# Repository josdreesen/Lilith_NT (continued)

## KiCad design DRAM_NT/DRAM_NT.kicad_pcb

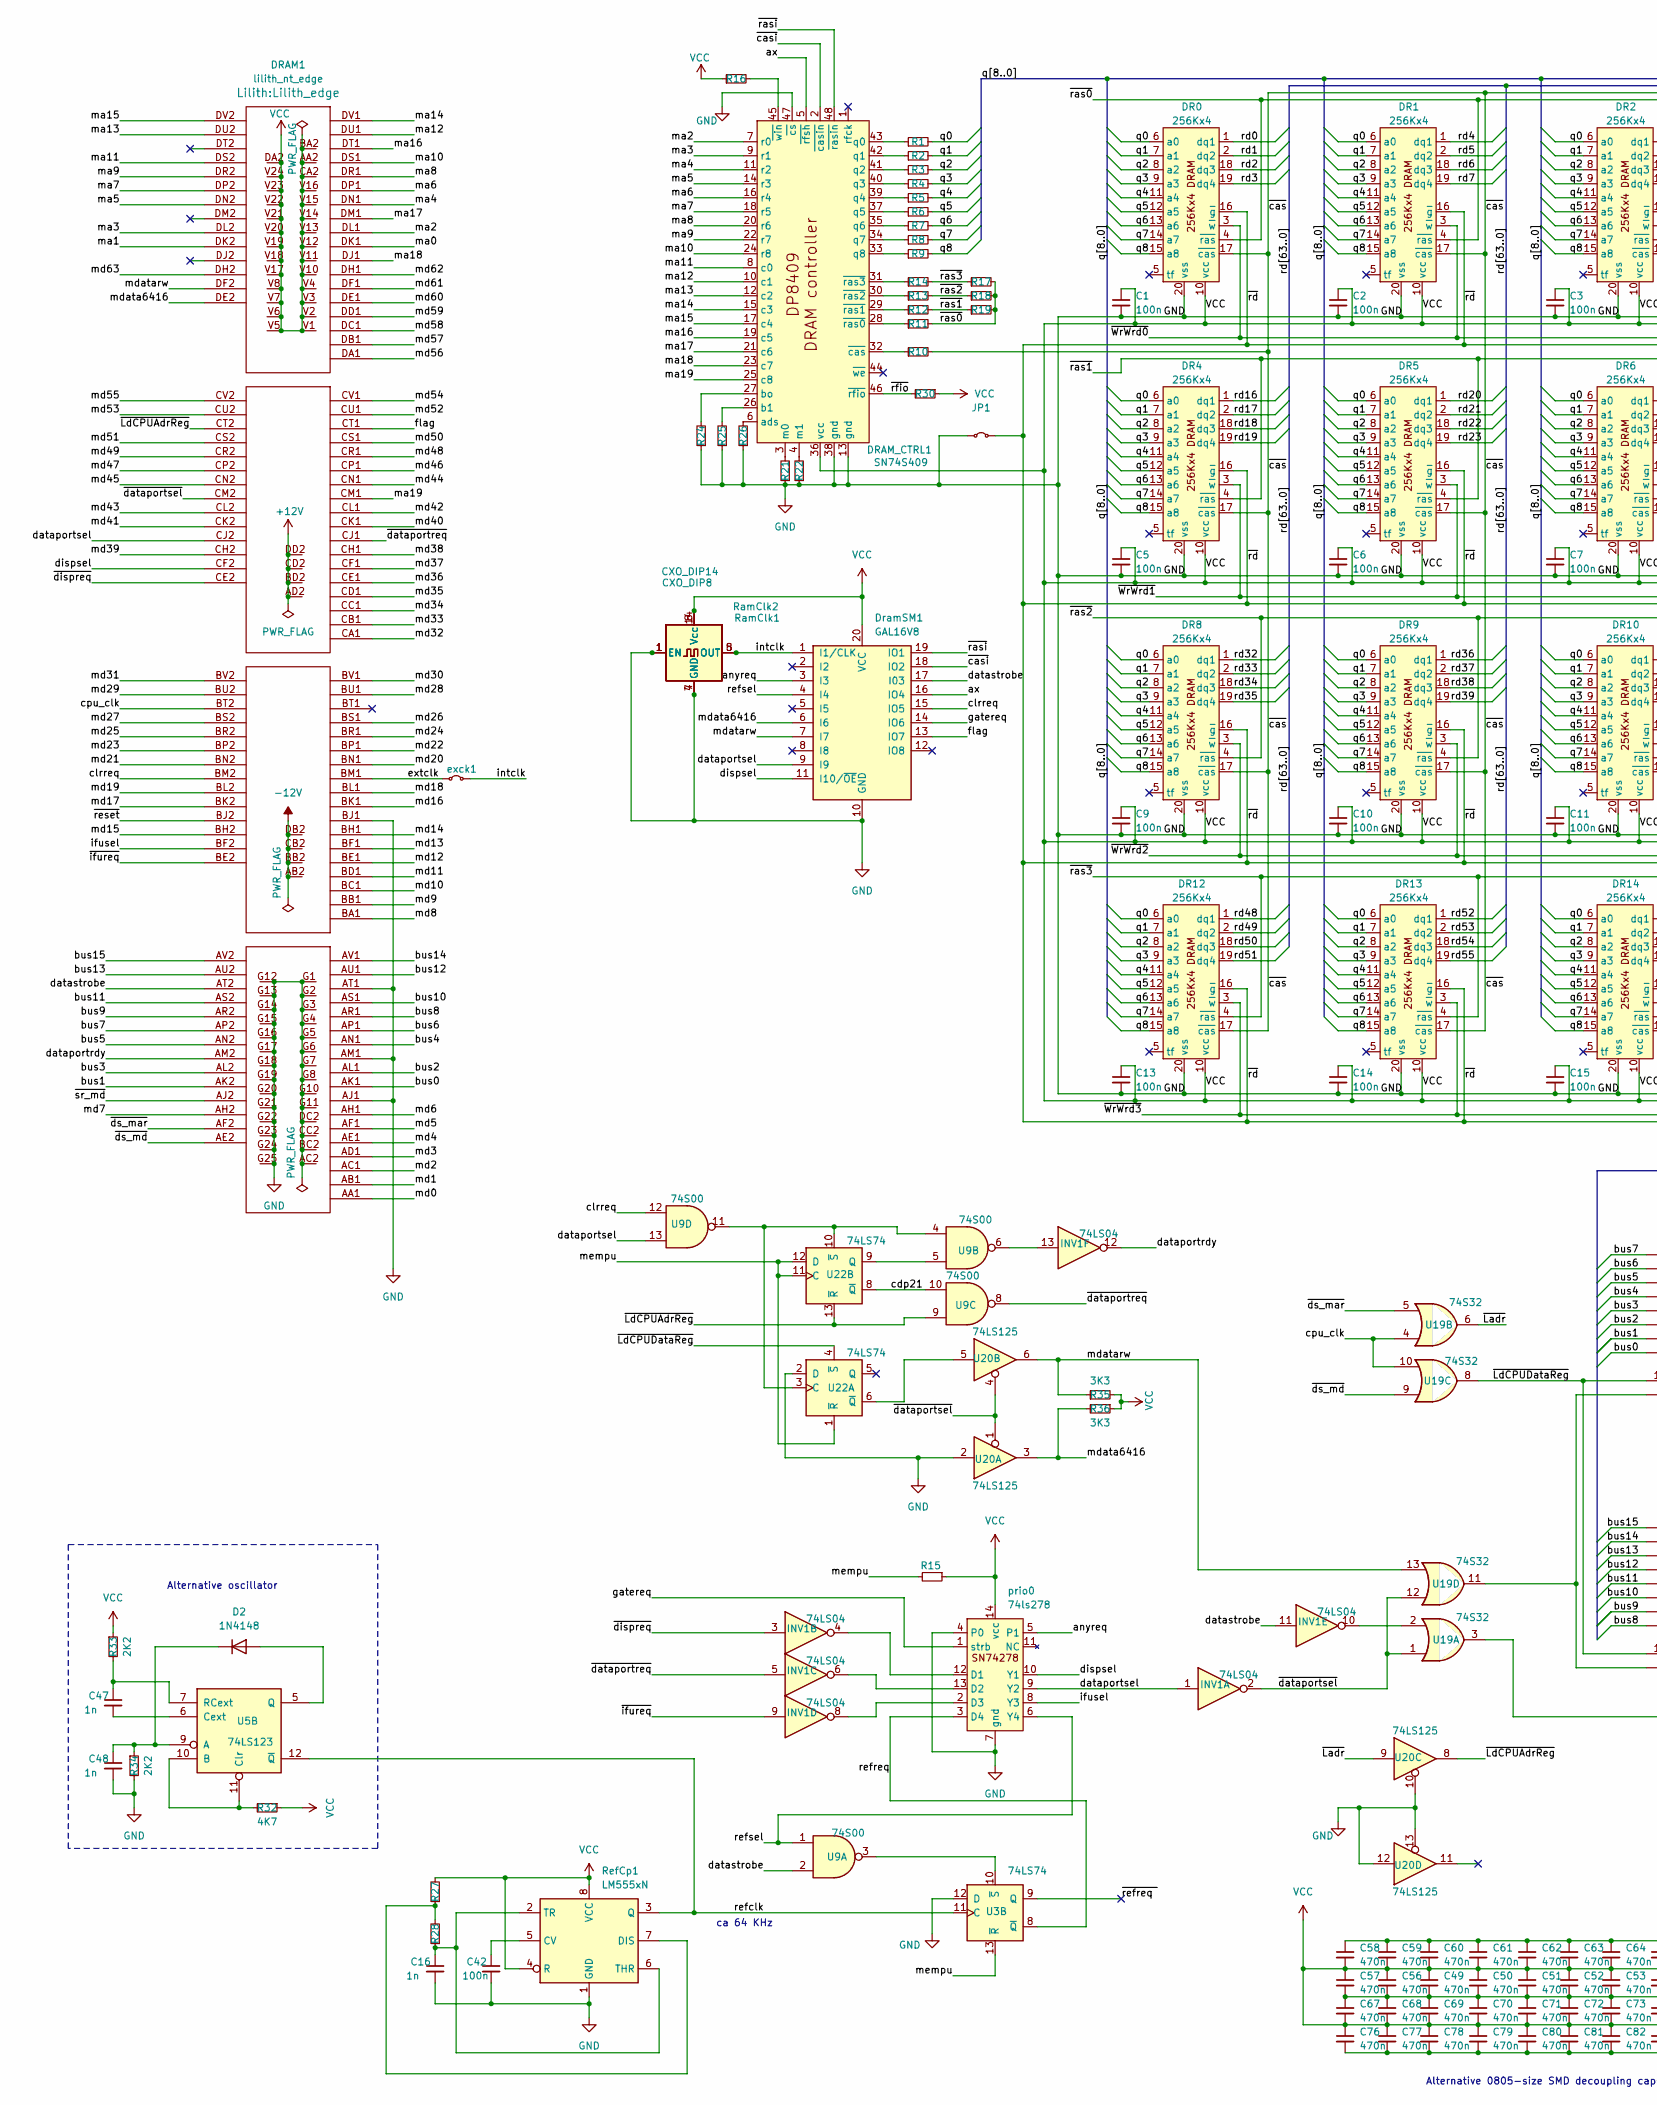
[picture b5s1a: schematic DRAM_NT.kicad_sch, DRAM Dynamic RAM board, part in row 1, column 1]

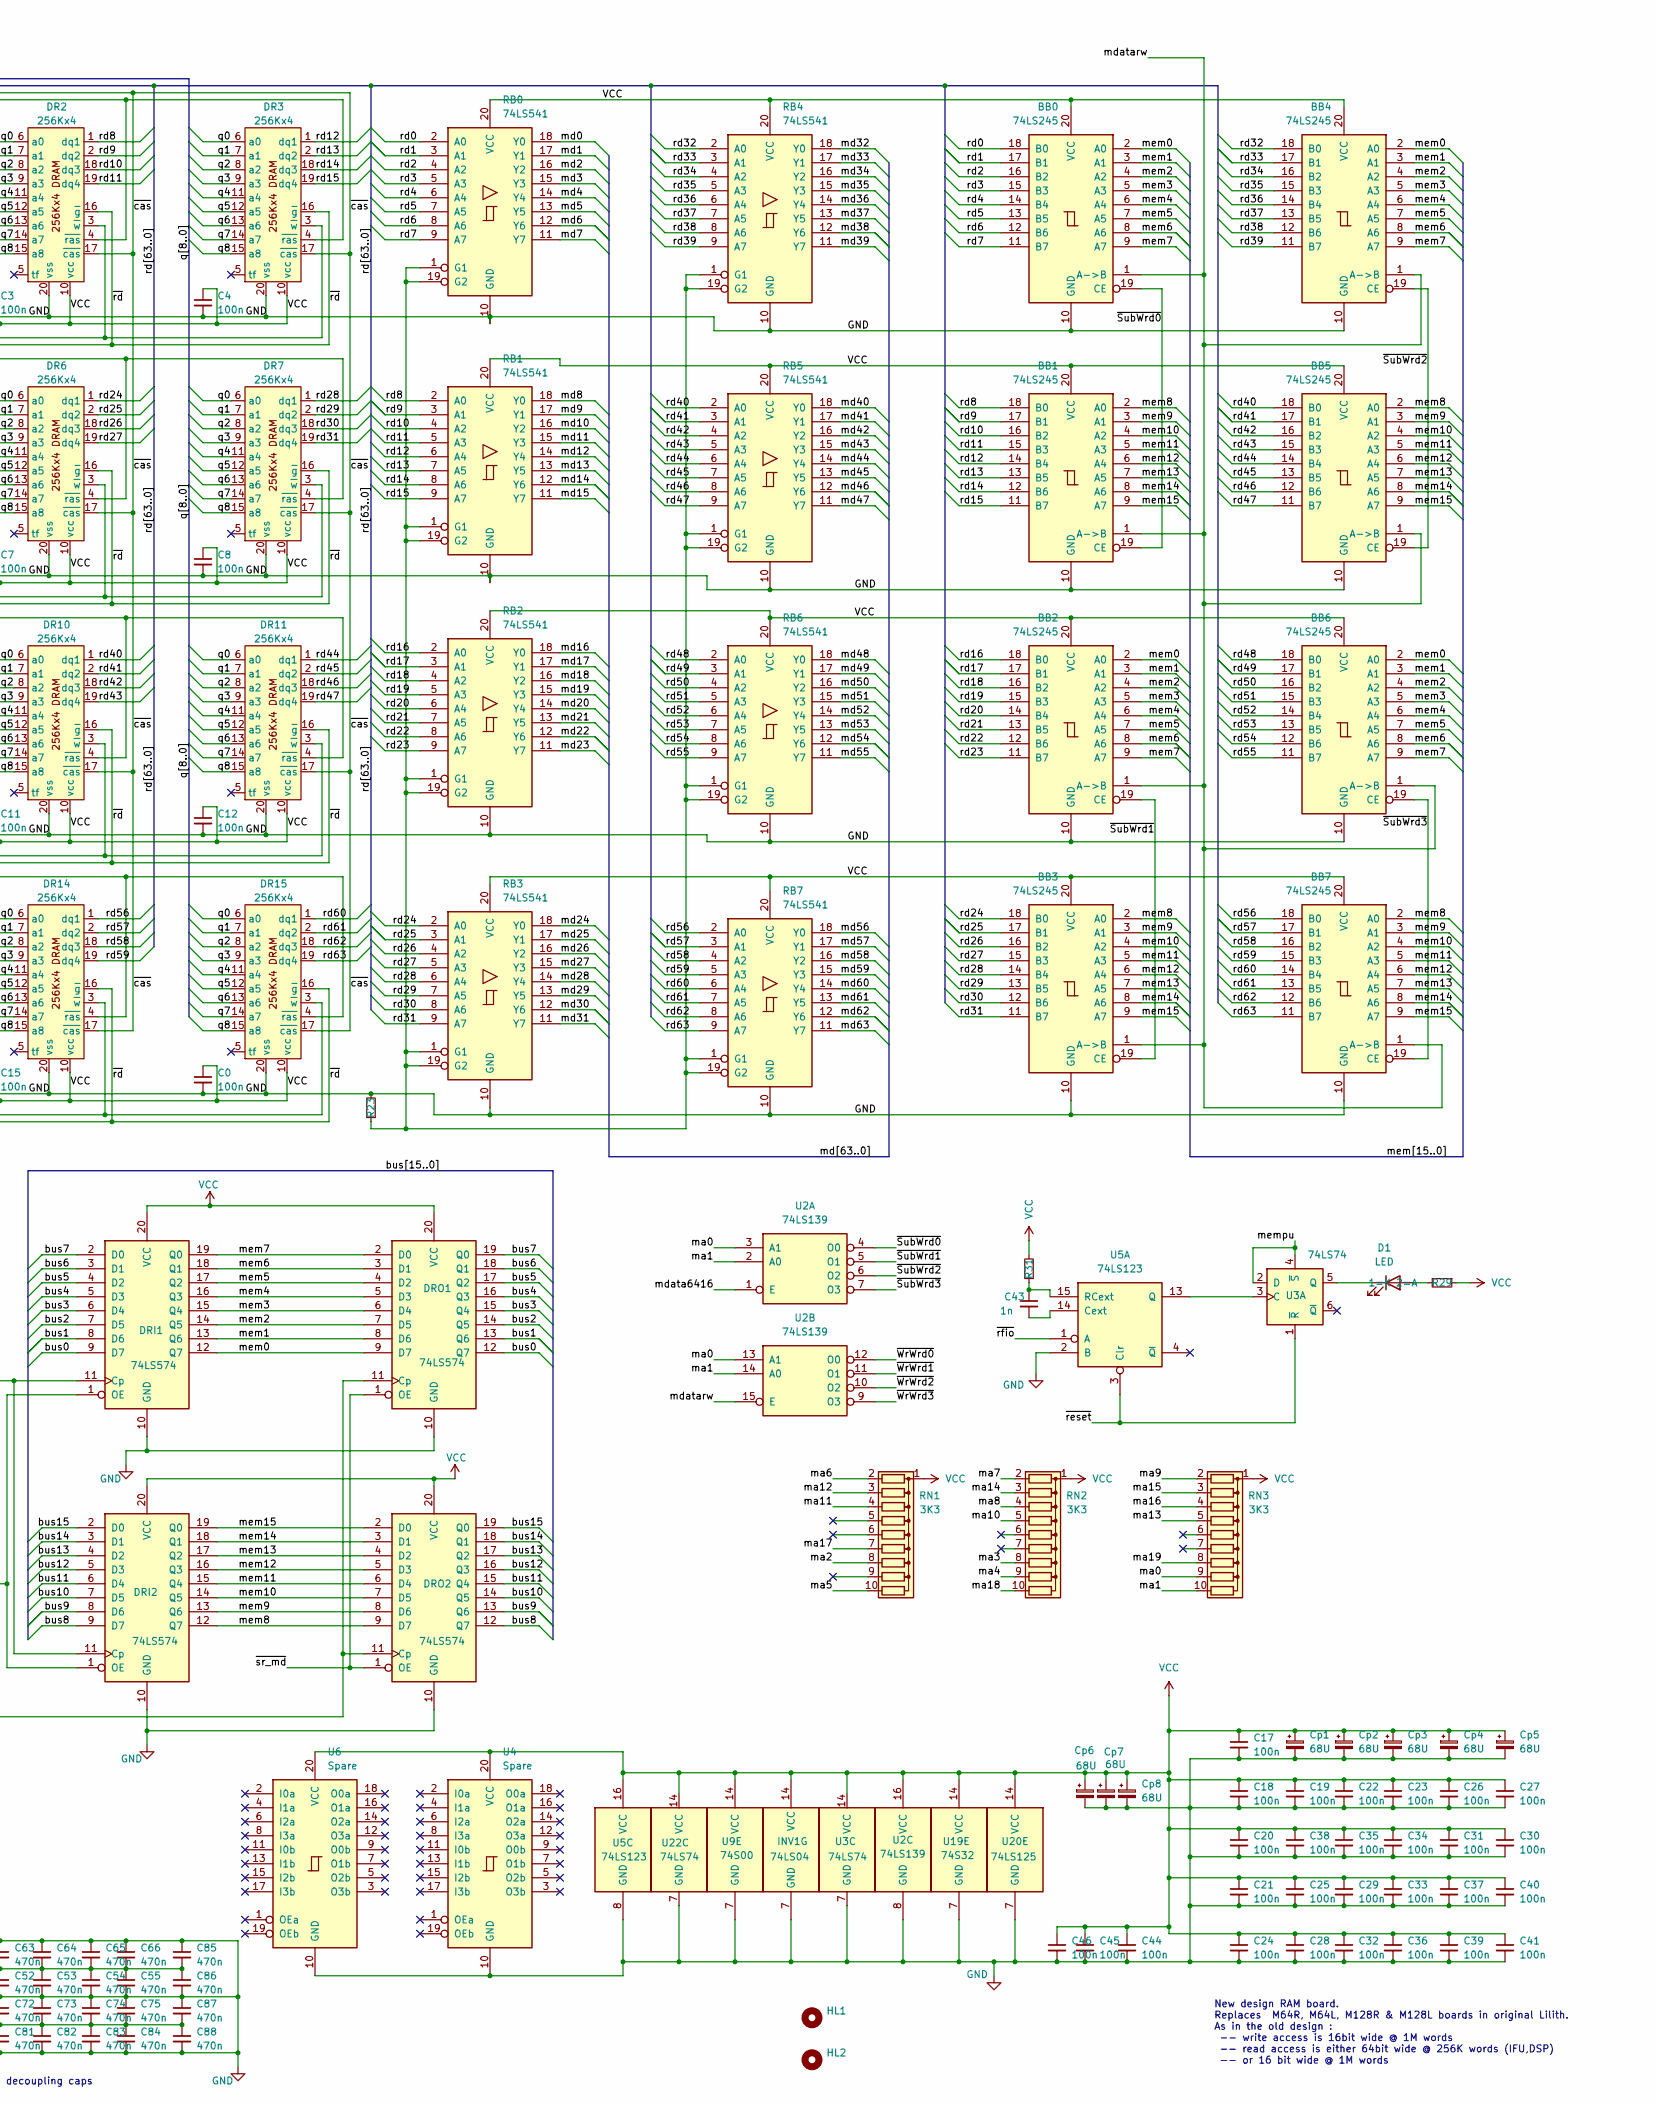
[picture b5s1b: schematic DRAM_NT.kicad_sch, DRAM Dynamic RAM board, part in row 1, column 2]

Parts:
BB0, BB1, BB2, BB3, BB4, BB5, BB6, BB7: 74LS245; DIP-20_W7.62mm
C0, C1, C2, C3, C4, C5, C6, C7, C8, C9, C10, C11, C12, C13, C14, C15, C18, C19, C20, C21, C22, C23, C24, C25, C26, C27, C28, C29, C30, C31, C32, C33, C34, C35, C36, C37, C38, C39, C40, C41, C44, C45, C46: 100n; C_1206_3216Metric_Pad1.33x1.80mm_HandSolder
C16, C43, C47, C48: 1n; C_Rect_L7.2mm_W3.5mm_P5.00mm_FKS2_FKP2_MKS2_MKP2
C17, C42: 100n; C_Rect_L7.2mm_W3.5mm_P5.00mm_FKS2_FKP2_MKS2_MKP2
C49, C50, C51, C52, C53, C54, C55, C56, C57, C58, C59, C60, C61, C62, C63, C64, C65, C66, C67, C68, C69, C70, C71, C72, C73, C74, C75, C76, C77, C78, C79, C80, C81, C82, C83, C84, C85, C86, C87, C88: 470n; C_0805_2012Metric_Pad1.18x1.45mm_HandSolder
Cp1, Cp2, Cp3, Cp4, Cp5: 68U; CP_PHP
Cp6, Cp7, Cp8: 68U; CP_EIA-7343-20_Kemet-V_HandSolder
D1: LED; LED_D5.0mm_Horizontal_O3.81mm_Z9.0mm
D2: 1N4148; D_DO-35_SOD27_P7.62mm_Horizontal
DR0, DR1, DR2, DR3, DR4, DR5, DR6, DR7, DR8, DR9, DR10, DR11, DR12, DR13, DR14, DR15: 256Kx4; DIP-20_W7.62mm
DRAM1: lilith_nt_edge; Lilith_edge
DRAM_CTRL1: SN74S409; DIP-48_W15.24mm
DRI1, DRI2: 74LS574; DIP-20_W7.62mm
DRO1, DRO2: 74LS574; DIP-20_W7.62mm
DramSM1: GAL16V8; DIP-20_W7.62mm_Socket
HL1, HL2: MountingHole; Handle
INV1: 74LS04; DIP-14_W7.62mm
JP1: Jumper_2_Small_Bridged; SolderJumper-2_P1.3mm_Bridged_RoundedPad1.0x1.5mm
R1, R2, R3, R4, R5, R6, R7, R8, R9, R10, R11, R12, R13, R14: 100; R_0805_2012Metric_Pad1.20x1.40mm_HandSolder
R15, R27, R28, R29, R30, R31: 100; R_Axial_DIN0207_L6.3mm_D2.5mm_P7.62mm_Horizontal
R16, R33, R34: 2K2; R_Axial_DIN0207_L6.3mm_D2.5mm_P7.62mm_Horizontal
R17, R18, R19, R21, R22, R23, R24, R25, R26: 0; R_0805_2012Metric_Pad1.20x1.40mm_HandSolder
R32: 4K7; R_Axial_DIN0207_L6.3mm_D2.5mm_P7.62mm_Horizontal
R35, R36: 3K3; R_Axial_DIN0207_L6.3mm_D2.5mm_P7.62mm_Horizontal
RB0, RB1, RB2, RB3, RB4, RB5, RB6, RB7: 74LS541; DIP-20_W7.62mm
RN1, RN2, RN3: 3K3; R_Array_SIP10
RamClk1: CXO_DIP14; Oscillator_DIP-14
RamClk2: CXO_DIP8; Oscillator_DIP-8
RefCp1: LM555xN; DIP-8_W7.62mm
U2: 74LS139; DIP-16_W7.62mm
U3, U22: 74LS74; DIP-14_W7.62mm
U4, U6: Spare; DIP-20_W7.62mm
U5: 74LS123; DIP-16_W7.62mm
U9: 74S00; DIP-14_W7.62mm
U19: 74S32; DIP-14_W7.62mm
U20: 74LS125; DIP-14_W7.62mm
exck1: Jumper_2_Small_Bridged; SolderJumper-2_P1.3mm_Bridged_RoundedPad1.0x1.5mm
prio0: 74ls278; DIP-14_W7.62mm

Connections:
+12V: DRAM1.AD2, DRAM1.BD2, DRAM1.CD2, DRAM1.DD2
-12V: DRAM1.AB2, DRAM1.BB2, DRAM1.CB2, DRAM1.DB2
/anyreq: DramSM1.3 (I3), prio0.5 (P1)
/ax: DRAM_CTRL1.5 (~rfsh), DramSM1.16 (IO4)
/bus0: DRAM1.AK1, DRI1.9 (D7), DRO1.12 (Q7)
/bus1: DRAM1.AK2, DRI1.8 (D6), DRO1.13 (Q6)
/bus2: DRAM1.AL1, DRI1.7 (D5), DRO1.14 (Q5)
/bus3: DRAM1.AL2, DRI1.6 (D4), DRO1.15 (Q4)
/bus4: DRAM1.AN1, DRI1.5 (D3), DRO1.16 (Q3)
/bus5: DRAM1.AN2, DRI1.4 (D2), DRO1.17 (Q2)
/bus6: DRAM1.AP1, DRI1.3 (D1), DRO1.18 (Q1)
/bus7: DRAM1.AP2, DRI1.2 (D0), DRO1.19 (Q0)
/bus8: DRAM1.AR1, DRI2.9 (D7), DRO2.12 (Q7)
/bus9: DRAM1.AR2, DRI2.8 (D6), DRO2.13 (Q6)
/bus10: DRAM1.AS1, DRI2.7 (D5), DRO2.14 (Q5)
/bus11: DRAM1.AS2, DRI2.6 (D4), DRO2.15 (Q4)
/bus12: DRAM1.AU1, DRI2.5 (D3), DRO2.16 (Q3)
/bus13: DRAM1.AU2, DRI2.4 (D2), DRO2.17 (Q2)
/bus14: DRAM1.AV1, DRI2.3 (D1), DRO2.18 (Q1)
/bus15: DRAM1.AV2, DRI2.2 (D0), DRO2.19 (Q0)
/cdp21: U9.10, U22.8 (~Q)
/clrreq: DRAM1.BM2, DramSM1.15 (IO5), U9.12
/cpu_clk: DRAM1.BT2, U19.4, U19.10
/dataportrdy: DRAM1.AM2, INV1.12
/dataportsel: DRAM1.CJ2, DramSM1.9 (I9), INV1.1, U9.13, prio0.9 (Y2)
/datastrobe: DRAM1.AT2, DramSM1.17 (I03), INV1.11, U9.2
/dispsel: DRAM1.CF2, DramSM1.11 (I10/~OE), prio0.10 (Y1)
/extclk: DRAM1.BM1, exck1.1 (A)
/flag: DRAM1.CT1, DramSM1.13 (IO7)
/gatereq: DramSM1.14 (IO6), prio0.1 (strb)
/ifusel: DRAM1.BF2, prio0.8 (Y3)
/intclk: DramSM1.1 (I1/CLK), RamClk1.8 (OUT), RamClk2.5 (OUT), exck1.2 (B)
/ma0: DRAM1.DK1, RN3.9 (R8), U2.3 (A1), U2.13 (A1)
/ma1: DRAM1.DK2, RN3.10 (R9), U2.2 (A0), U2.14 (A0)
/ma2: DRAM1.DL1, DRAM_CTRL1.7 (r0), RN1.8 (R7)
/ma3: DRAM1.DL2, DRAM_CTRL1.9 (r1), RN2.8 (R7)
/ma4: DRAM1.DN1, DRAM_CTRL1.11 (r2), RN2.9 (R8)
/ma5: DRAM1.DN2, DRAM_CTRL1.14 (r3), RN1.10 (R9)
/ma6: DRAM1.DP1, DRAM_CTRL1.16 (r4), RN1.2 (R1)
/ma7: DRAM1.DP2, DRAM_CTRL1.18 (r5), RN2.2 (R1)
/ma8: DRAM1.DR1, DRAM_CTRL1.20 (r6), RN2.4 (R3)
/ma9: DRAM1.DR2, DRAM_CTRL1.22 (r7), RN3.2 (R1)
/ma10: DRAM1.DS1, DRAM_CTRL1.24 (r8), RN2.5 (R4)
/ma11: DRAM1.DS2, DRAM_CTRL1.8 (c0), RN1.4 (R3)
/ma12: DRAM1.DU1, DRAM_CTRL1.10 (c1), RN1.3 (R2)
/ma13: DRAM1.DU2, DRAM_CTRL1.12 (c2), RN3.5 (R4)
/ma14: DRAM1.DV1, DRAM_CTRL1.15 (c3), RN2.3 (R2)
/ma15: DRAM1.DV2, DRAM_CTRL1.17 (c4), RN3.3 (R2)
/ma16: DRAM1.DT1, DRAM_CTRL1.19 (c5), RN3.4 (R3)
/ma17: DRAM1.DM1, DRAM_CTRL1.21 (c6), RN1.7 (R6)
/ma18: DRAM1.DJ1, DRAM_CTRL1.23 (c7), RN2.10 (R9)
/ma19: DRAM1.CM1, DRAM_CTRL1.25 (c8), RN3.8 (R7)
/md0: DRAM1.AA1, RB0.18 (Y0)
/md1: DRAM1.AB1, RB0.17 (Y1)
/md2: DRAM1.AC1, RB0.16 (Y2)
/md3: DRAM1.AD1, RB0.15 (Y3)
/md4: DRAM1.AE1, RB0.14 (Y4)
/md5: DRAM1.AF1, RB0.13 (Y5)
/md6: DRAM1.AH1, RB0.12 (Y6)
/md7: DRAM1.AH2, RB0.11 (Y7)
/md8: DRAM1.BA1, RB1.18 (Y0)
/md9: DRAM1.BB1, RB1.17 (Y1)
/md10: DRAM1.BC1, RB1.16 (Y2)
/md11: DRAM1.BD1, RB1.15 (Y3)
/md12: DRAM1.BE1, RB1.14 (Y4)
/md13: DRAM1.BF1, RB1.13 (Y5)
/md14: DRAM1.BH1, RB1.12 (Y6)
/md15: DRAM1.BH2, RB1.11 (Y7)
/md16: DRAM1.BK1, RB2.18 (Y0)
/md17: DRAM1.BK2, RB2.17 (Y1)
/md18: DRAM1.BL1, RB2.16 (Y2)
/md19: DRAM1.BL2, RB2.15 (Y3)
/md20: DRAM1.BN1, RB2.14 (Y4)
/md21: DRAM1.BN2, RB2.13 (Y5)
/md22: DRAM1.BP1, RB2.12 (Y6)
/md23: DRAM1.BP2, RB2.11 (Y7)
/md24: DRAM1.BR1, RB3.18 (Y0)
/md25: DRAM1.BR2, RB3.17 (Y1)
/md26: DRAM1.BS1, RB3.16 (Y2)
/md27: DRAM1.BS2, RB3.15 (Y3)
/md28: DRAM1.BU1, RB3.14 (Y4)
/md29: DRAM1.BU2, RB3.13 (Y5)
/md30: DRAM1.BV1, RB3.12 (Y6)
/md31: DRAM1.BV2, RB3.11 (Y7)
/md32: DRAM1.CA1, RB4.18 (Y0)
/md33: DRAM1.CB1, RB4.17 (Y1)
/md34: DRAM1.CC1, RB4.16 (Y2)
/md35: DRAM1.CD1, RB4.15 (Y3)
/md36: DRAM1.CE1, RB4.14 (Y4)
/md37: DRAM1.CF1, RB4.13 (Y5)
/md38: DRAM1.CH1, RB4.12 (Y6)
/md39: DRAM1.CH2, RB4.11 (Y7)
/md40: DRAM1.CK1, RB5.18 (Y0)
/md41: DRAM1.CK2, RB5.17 (Y1)
/md42: DRAM1.CL1, RB5.16 (Y2)
/md43: DRAM1.CL2, RB5.15 (Y3)
/md44: DRAM1.CN1, RB5.14 (Y4)
/md45: DRAM1.CN2, RB5.13 (Y5)
/md46: DRAM1.CP1, RB5.12 (Y6)
/md47: DRAM1.CP2, RB5.11 (Y7)
/md48: DRAM1.CR1, RB6.18 (Y0)
/md49: DRAM1.CR2, RB6.17 (Y1)
/md50: DRAM1.CS1, RB6.16 (Y2)
/md51: DRAM1.CS2, RB6.15 (Y3)
/md52: DRAM1.CU1, RB6.14 (Y4)
/md53: DRAM1.CU2, RB6.13 (Y5)
/md54: DRAM1.CV1, RB6.12 (Y6)
/md55: DRAM1.CV2, RB6.11 (Y7)
/md56: DRAM1.DA1, RB7.18 (Y0)
/md57: DRAM1.DB1, RB7.17 (Y1)
/md58: DRAM1.DC1, RB7.16 (Y2)
/md59: DRAM1.DD1, RB7.15 (Y3)
/md60: DRAM1.DE1, RB7.14 (Y4)
/md61: DRAM1.DF1, RB7.13 (Y5)
/md62: DRAM1.DH1, RB7.12 (Y6)
/md63: DRAM1.DH2, RB7.11 (Y7)
/mdata6416: DRAM1.DE2, DramSM1.6 (I6), R36.2, U2.1 (E), U20.3
/mdatarw: BB0.1 (A->B), BB1.1 (A->B), BB2.1 (A->B), BB3.1 (A->B), BB4.1 (A->B), BB5.1 (A->B), BB6.1 (A->B), BB7.1 (A->B), DRAM1.DF2, DramSM1.7 (I7), R35.1, U2.15 (E), U19.13, U20.6
/mem0: BB0.2 (A0), BB2.2 (A0), BB4.2 (A0), BB6.2 (A0), DRI1.12 (Q7), DRO1.9 (D7)
/mem1: BB0.3 (A1), BB2.3 (A1), BB4.3 (A1), BB6.3 (A1), DRI1.13 (Q6), DRO1.8 (D6)
/mem2: BB0.4 (A2), BB2.4 (A2), BB4.4 (A2), BB6.4 (A2), DRI1.14 (Q5), DRO1.7 (D5)
/mem3: BB0.5 (A3), BB2.5 (A3), BB4.5 (A3), BB6.5 (A3), DRI1.15 (Q4), DRO1.6 (D4)
/mem4: BB0.6 (A4), BB2.6 (A4), BB4.6 (A4), BB6.6 (A4), DRI1.16 (Q3), DRO1.5 (D3)
/mem5: BB0.7 (A5), BB2.7 (A5), BB4.7 (A5), BB6.7 (A5), DRI1.17 (Q2), DRO1.4 (D2)
/mem6: BB0.8 (A6), BB2.8 (A6), BB4.8 (A6), BB6.8 (A6), DRI1.18 (Q1), DRO1.3 (D1)
/mem7: BB0.9 (A7), BB2.9 (A7), BB4.9 (A7), BB6.9 (A7), DRI1.19 (Q0), DRO1.2 (D0)
/mem8: BB1.2 (A0), BB3.2 (A0), BB5.2 (A0), BB7.2 (A0), DRI2.12 (Q7), DRO2.9 (D7)
/mem9: BB1.3 (A1), BB3.3 (A1), BB5.3 (A1), BB7.3 (A1), DRI2.13 (Q6), DRO2.8 (D6)
/mem10: BB1.4 (A2), BB3.4 (A2), BB5.4 (A2), BB7.4 (A2), DRI2.14 (Q5), DRO2.7 (D5)
/mem11: BB1.5 (A3), BB3.5 (A3), BB5.5 (A3), BB7.5 (A3), DRI2.15 (Q4), DRO2.6 (D4)
/mem12: BB1.6 (A4), BB3.6 (A4), BB5.6 (A4), BB7.6 (A4), DRI2.16 (Q3), DRO2.5 (D3)
/mem13: BB1.7 (A5), BB3.7 (A5), BB5.7 (A5), BB7.7 (A5), DRI2.17 (Q2), DRO2.4 (D2)
/mem14: BB1.8 (A6), BB3.8 (A6), BB5.8 (A6), BB7.8 (A6), DRI2.18 (Q1), DRO2.3 (D1)
/mem15: BB1.9 (A7), BB3.9 (A7), BB5.9 (A7), BB7.9 (A7), DRI2.19 (Q0), DRO2.2 (D0)
/mempu: R15.2, U3.2 (D), U3.4 (~S), U3.13 (~R), U22.1 (~R), U22.11 (C), U22.12 (D)
/q0: DR0.6 (a0), DR1.6 (a0), DR2.6 (a0), DR3.6 (a0), DR4.6 (a0), DR5.6 (a0), DR6.6 (a0), DR7.6 (a0), DR8.6 (a0), DR9.6 (a0), DR10.6 (a0), DR11.6 (a0), DR12.6 (a0), DR13.6 (a0), DR14.6 (a0), DR15.6 (a0), R1.2
/q1: DR0.7 (a1), DR1.7 (a1), DR2.7 (a1), DR3.7 (a1), DR4.7 (a1), DR5.7 (a1), DR6.7 (a1), DR7.7 (a1), DR8.7 (a1), DR9.7 (a1), DR10.7 (a1), DR11.7 (a1), DR12.7 (a1), DR13.7 (a1), DR14.7 (a1), DR15.7 (a1), R2.2
/q2: DR0.8 (a2), DR1.8 (a2), DR2.8 (a2), DR3.8 (a2), DR4.8 (a2), DR5.8 (a2), DR6.8 (a2), DR7.8 (a2), DR8.8 (a2), DR9.8 (a2), DR10.8 (a2), DR11.8 (a2), DR12.8 (a2), DR13.8 (a2), DR14.8 (a2), DR15.8 (a2), R3.2
/q3: DR0.9 (a3), DR1.9 (a3), DR2.9 (a3), DR3.9 (a3), DR4.9 (a3), DR5.9 (a3), DR6.9 (a3), DR7.9 (a3), DR8.9 (a3), DR9.9 (a3), DR10.9 (a3), DR11.9 (a3), DR12.9 (a3), DR13.9 (a3), DR14.9 (a3), DR15.9 (a3), R4.2
/q4: DR0.11 (a4), DR1.11 (a4), DR2.11 (a4), DR3.11 (a4), DR4.11 (a4), DR5.11 (a4), DR6.11 (a4), DR7.11 (a4), DR8.11 (a4), DR9.11 (a4), DR10.11 (a4), DR11.11 (a4), DR12.11 (a4), DR13.11 (a4), DR14.11 (a4), DR15.11 (a4), R5.2
/q5: DR0.12 (a5), DR1.12 (a5), DR2.12 (a5), DR3.12 (a5), DR4.12 (a5), DR5.12 (a5), DR6.12 (a5), DR7.12 (a5), DR8.12 (a5), DR9.12 (a5), DR10.12 (a5), DR11.12 (a5), DR12.12 (a5), DR13.12 (a5), DR14.12 (a5), DR15.12 (a5), R6.2
/q6: DR0.13 (a6), DR1.13 (a6), DR2.13 (a6), DR3.13 (a6), DR4.13 (a6), DR5.13 (a6), DR6.13 (a6), DR7.13 (a6), DR8.13 (a6), DR9.13 (a6), DR10.13 (a6), DR11.13 (a6), DR12.13 (a6), DR13.13 (a6), DR14.13 (a6), DR15.13 (a6), R7.2
/q7: DR0.14 (a7), DR1.14 (a7), DR2.14 (a7), DR3.14 (a7), DR4.14 (a7), DR5.14 (a7), DR6.14 (a7), DR7.14 (a7), DR8.14 (a7), DR9.14 (a7), DR10.14 (a7), DR11.14 (a7), DR12.14 (a7), DR13.14 (a7), DR14.14 (a7), DR15.14 (a7), R8.2
/q8: DR0.15 (a8), DR1.15 (a8), DR2.15 (a8), DR3.15 (a8), DR4.15 (a8), DR5.15 (a8), DR6.15 (a8), DR7.15 (a8), DR8.15 (a8), DR9.15 (a8), DR10.15 (a8), DR11.15 (a8), DR12.15 (a8), DR13.15 (a8), DR14.15 (a8), DR15.15 (a8), R9.2
/rd0: BB0.18 (B0), DR0.1 (dq1), RB0.2 (A0)
/rd1: BB0.17 (B1), DR0.2 (dq2), RB0.3 (A1)
/rd2: BB0.16 (B2), DR0.18 (dq3), RB0.4 (A2)
/rd3: BB0.15 (B3), DR0.19 (dq4), RB0.5 (A3)
/rd4: BB0.14 (B4), DR1.1 (dq1), RB0.6 (A4)
/rd5: BB0.13 (B5), DR1.2 (dq2), RB0.7 (A5)
/rd6: BB0.12 (B6), DR1.18 (dq3), RB0.8 (A6)
/rd7: BB0.11 (B7), DR1.19 (dq4), RB0.9 (A7)
/rd8: BB1.18 (B0), DR2.1 (dq1), RB1.2 (A0)
/rd9: BB1.17 (B1), DR2.2 (dq2), RB1.3 (A1)
/rd10: BB1.16 (B2), DR2.18 (dq3), RB1.4 (A2)
/rd11: BB1.15 (B3), DR2.19 (dq4), RB1.5 (A3)
/rd12: BB1.14 (B4), DR3.1 (dq1), RB1.6 (A4)
/rd13: BB1.13 (B5), DR3.2 (dq2), RB1.7 (A5)
/rd14: BB1.12 (B6), DR3.18 (dq3), RB1.8 (A6)
/rd15: BB1.11 (B7), DR3.19 (dq4), RB1.9 (A7)
/rd16: BB2.18 (B0), DR4.1 (dq1), RB2.2 (A0)
/rd17: BB2.17 (B1), DR4.2 (dq2), RB2.3 (A1)
/rd18: BB2.16 (B2), DR4.18 (dq3), RB2.4 (A2)
/rd19: BB2.15 (B3), DR4.19 (dq4), RB2.5 (A3)
/rd20: BB2.14 (B4), DR5.1 (dq1), RB2.6 (A4)
/rd21: BB2.13 (B5), DR5.2 (dq2), RB2.7 (A5)
/rd22: BB2.12 (B6), DR5.18 (dq3), RB2.8 (A6)
/rd23: BB2.11 (B7), DR5.19 (dq4), RB2.9 (A7)
/rd24: BB3.18 (B0), DR6.1 (dq1), RB3.2 (A0)
/rd25: BB3.17 (B1), DR6.2 (dq2), RB3.3 (A1)
/rd26: BB3.16 (B2), DR6.18 (dq3), RB3.4 (A2)
/rd27: BB3.15 (B3), DR6.19 (dq4), RB3.5 (A3)
/rd28: BB3.14 (B4), DR7.1 (dq1), RB3.6 (A4)
/rd29: BB3.13 (B5), DR7.2 (dq2), RB3.7 (A5)
/rd30: BB3.12 (B6), DR7.18 (dq3), RB3.8 (A6)
/rd31: BB3.11 (B7), DR7.19 (dq4), RB3.9 (A7)
/rd32: BB4.18 (B0), DR8.1 (dq1), RB4.2 (A0)
/rd33: BB4.17 (B1), DR8.2 (dq2), RB4.3 (A1)
/rd34: BB4.16 (B2), DR8.18 (dq3), RB4.4 (A2)
/rd35: BB4.15 (B3), DR8.19 (dq4), RB4.5 (A3)
/rd36: BB4.14 (B4), DR9.1 (dq1), RB4.6 (A4)
/rd37: BB4.13 (B5), DR9.2 (dq2), RB4.7 (A5)
/rd38: BB4.12 (B6), DR9.18 (dq3), RB4.8 (A6)
/rd39: BB4.11 (B7), DR9.19 (dq4), RB4.9 (A7)
/rd40: BB5.18 (B0), DR10.1 (dq1), RB5.2 (A0)
/rd41: BB5.17 (B1), DR10.2 (dq2), RB5.3 (A1)
/rd42: BB5.16 (B2), DR10.18 (dq3), RB5.4 (A2)
/rd43: BB5.15 (B3), DR10.19 (dq4), RB5.5 (A3)
/rd44: BB5.14 (B4), DR11.1 (dq1), RB5.6 (A4)
/rd45: BB5.13 (B5), DR11.2 (dq2), RB5.7 (A5)
/rd46: BB5.12 (B6), DR11.18 (dq3), RB5.8 (A6)
/rd47: BB5.11 (B7), DR11.19 (dq4), RB5.9 (A7)
/rd48: BB6.18 (B0), DR12.1 (dq1), RB6.2 (A0)
/rd49: BB6.17 (B1), DR12.2 (dq2), RB6.3 (A1)
/rd50: BB6.16 (B2), DR12.18 (dq3), RB6.4 (A2)
/rd51: BB6.15 (B3), DR12.19 (dq4), RB6.5 (A3)
/rd52: BB6.14 (B4), DR13.1 (dq1), RB6.6 (A4)
/rd53: BB6.13 (B5), DR13.2 (dq2), RB6.7 (A5)
/rd54: BB6.12 (B6), DR13.18 (dq3), RB6.8 (A6)
/rd55: BB6.11 (B7), DR13.19 (dq4), RB6.9 (A7)
/rd56: BB7.18 (B0), DR14.1 (dq1), RB7.2 (A0)
/rd57: BB7.17 (B1), DR14.2 (dq2), RB7.3 (A1)
/rd58: BB7.16 (B2), DR14.18 (dq3), RB7.4 (A2)
/rd59: BB7.15 (B3), DR14.19 (dq4), RB7.5 (A3)
/rd60: BB7.14 (B4), DR15.1 (dq1), RB7.6 (A4)
/rd61: BB7.13 (B5), DR15.2 (dq2), RB7.7 (A5)
/rd62: BB7.12 (B6), DR15.18 (dq3), RB7.8 (A6)
/rd63: BB7.11 (B7), DR15.19 (dq4), RB7.9 (A7)
/refclk: RefCp1.3 (Q), U3.11 (C), U5.12 (~Q)
/refreq: U3.8 (~Q), prio0.3 (D4)
/refsel: DramSM1.4 (I4), U9.1, prio0.6 (Y4)
/~Ladr: U19.6, U20.9
/~LdCPUAdrReg: DRAM1.CT2, U9.9, U20.8, U22.13 (~R)
/~LdCPUDataReg: DRI1.11 (Cp), DRI2.11 (Cp), U19.8, U22.4 (~S)
/~SubWrd0: BB0.19 (CE), BB1.19 (CE), U2.4 (O0)
/~SubWrd1: BB2.19 (CE), BB3.19 (CE), U2.5 (O1)
/~SubWrd2: BB4.19 (CE), BB5.19 (CE), U2.6 (O2)
/~SubWrd3: BB6.19 (CE), BB7.19 (CE), U2.7 (O3)
/~WrWrd0: DR0.3 (~w), DR1.3 (~w), DR2.3 (~w), DR3.3 (~w), U2.12 (O0)
/~WrWrd1: DR4.3 (~w), DR5.3 (~w), DR6.3 (~w), DR7.3 (~w), U2.11 (O1)
/~WrWrd2: DR8.3 (~w), DR9.3 (~w), DR10.3 (~w), DR11.3 (~w), U2.10 (O2)
/~WrWrd3: DR12.3 (~w), DR13.3 (~w), DR14.3 (~w), DR15.3 (~w), U2.9 (O3)
/~casi: DRAM_CTRL1.2 (~casin), DramSM1.18 (IO2)
/~cas: DR0.17 (~cas), DR1.17 (~cas), DR2.17 (~cas), DR3.17 (~cas), DR4.17 (~cas), DR5.17 (~cas), DR6.17 (~cas), DR7.17 (~cas), DR8.17 (~cas), DR9.17 (~cas), DR10.17 (~cas), DR11.17 (~cas), DR12.17 (~cas), DR13.17 (~cas), DR14.17 (~cas), DR15.17 (~cas), R10.2
/~dataportreq: DRAM1.CJ1, INV1.5, U9.8
/~dataportsel: DRAM1.CM2, INV1.2, U19.1, U19.12, U20.1, U20.4
/~dispreq: DRAM1.CE2, INV1.3
/~ds_mar: DRAM1.AF2, U19.5
/~ds_md: DRAM1.AE2, U19.9
/~ifureq: DRAM1.BE2, INV1.9
/~ras0: DR0.4 (~ras), DR1.4 (~ras), DR2.4 (~ras), DR3.4 (~ras), R11.2, R17.2, R18.2, R19.2
/~ras1: DR4.4 (~ras), DR5.4 (~ras), DR6.4 (~ras), DR7.4 (~ras), R12.2, R19.1
/~ras2: DR8.4 (~ras), DR9.4 (~ras), DR10.4 (~ras), DR11.4 (~ras), R13.2, R18.1
/~ras3: DR12.4 (~ras), DR13.4 (~ras), DR14.4 (~ras), DR15.4 (~ras), R14.2, R17.1
/~rasi: DRAM_CTRL1.48 (~rasin), DramSM1.19 (IO1)
/~rd: DR0.16 (~g), DR1.16 (~g), DR2.16 (~g), DR3.16 (~g), DR4.16 (~g), DR5.16 (~g), DR6.16 (~g), DR7.16 (~g), DR8.16 (~g), DR9.16 (~g), DR10.16 (~g), DR11.16 (~g), DR12.16 (~g), DR13.16 (~g), DR14.16 (~g), DR15.16 (~g), JP1.2 (B)
/~refreq: U3.9 (Q)
/~reset: DRAM1.BJ2, U3.1 (~R), U5.3 (Clr)
/~rfio: DRAM_CTRL1.46 (~rfio), R30.2, U5.1 (A)
/~sr_md: DRAM1.AJ2, DRO1.1 (OE), DRO2.1 (OE)
GND: BB0.10 (GND), BB1.10 (GND), BB2.10 (GND), BB3.10 (GND), BB4.10 (GND), BB5.10 (GND), BB6.10 (GND), BB7.10 (GND), C0.2, C1.2, C2.2, C3.2, C4.2, C5.2, C6.2, C7.2, C8.2, C9.2, C10.2, C11.2, C12.2, C13.2, C14.2, C15.2, C16.2, C17.2, C18.2, C19.2, C20.2, C21.2, C22.2, C23.2, C24.2, C25.2, C26.2, C27.2, C28.2, C29.2, C30.2, C31.2, C32.2, C33.2, C34.2, C35.2, C36.2, C37.2, C38.2, C39.2, C40.2, C41.2, C42.2, C44.2, C45.2, C46.2, C48.2, C49.2, C50.2, C51.2, C52.2, C53.2, C54.2, C55.2, C56.2, C57.2, C58.1, C59.1, C60.1, C61.1, C62.1, C63.1, C64.1, C65.1, C66.1, C67.1, C68.1, C69.1, C70.1, C71.1, C72.1, C73.1, C74.1, C75.1, C76.2, C77.2, C78.2, C79.2, C80.2, C81.2, C82.2, C83.2, C84.2, C85.1, C86.2, C87.1, C88.2, Cp1.2, Cp2.2, Cp3.2, Cp4.2, Cp5.2, Cp6.2, Cp7.2, Cp8.2, DR0.20 (vss), DR1.20 (vss), DR2.20 (vss), DR3.20 (vss), DR4.20 (vss), DR5.20 (vss), DR6.20 (vss), DR7.20 (vss), DR8.20 (vss), DR9.20 (vss), DR10.20 (vss), DR11.20 (vss), DR12.20 (vss), DR13.20 (vss), DR14.20 (vss), DR15.20 (vss), DRAM1.AC2, DRAM1.AJ1, DRAM1.AM1, DRAM1.AT1, DRAM1.BC2, DRAM1.BJ1, DRAM1.CC2, DRAM1.DC2, DRAM1.G1 (GND), DRAM1.G2 (GND), DRAM1.G3 (GND), DRAM1.G4 (GND), DRAM1.G5 (GND), DRAM1.G6 (GND), DRAM1.G7 (GND), DRAM1.G8 (GND), DRAM1.G10, DRAM1.G11, DRAM1.G12, DRAM1.G13, DRAM1.G14, DRAM1.G15, DRAM1.G16, DRAM1.G17, DRAM1.G18, DRAM1.G19, DRAM1.G20, DRAM1.G21, DRAM1.G22, DRAM1.G23, DRAM1.G24, DRAM1.G25, DRAM_CTRL1.13 (gnd), DRAM_CTRL1.38 (gnd), DRAM_CTRL1.47 (~cs), DRI1.10 (GND), DRI2.10 (GND), DRO1.10 (GND), DRO2.10 (GND), DramSM1.10 (GND), INV1.7 (GND), JP1.1 (A), R21.1, R22.1, R23.2, R24.1, R25.1, R26.1, R34.2, RB0.10 (GND), RB1.10 (GND), RB2.10 (GND), RB3.10 (GND), RB4.10 (GND), RB5.10 (GND), RB6.10 (GND), RB7.10 (GND), RamClk1.1 (EN), RamClk1.7 (GND), RamClk2.1 (EN), RamClk2.4 (GND), RefCp1.1 (GND), U2.8 (GND), U3.7 (GND), U3.12 (D), U4.10 (GND), U5.2 (B), U5.8 (GND), U6.10 (GND), U9.7 (GND), U19.7 (GND), U20.2, U20.7 (GND), U20.10, U20.12, U20.13, U22.2 (D), U22.7 (GND), prio0.4 (P0), prio0.7 (gnd)
unnamed: D1.2 (A), R29.2
unnamed: D1.1 (K), U3.5 (Q)
unnamed: D2.2 (A), U5.5 (Q)
unnamed: C48.1, D2.1 (K), R34.1, U5.9 (A)
unnamed: DRAM_CTRL1.6 (ads), R26.2
unnamed: DRAM_CTRL1.26 (b1), R25.2
unnamed: DRAM_CTRL1.27 (bo), R24.2
unnamed: DRAM_CTRL1.3 (m0), R21.2
unnamed: DRAM_CTRL1.4 (m1), R22.2
unnamed: DRAM_CTRL1.43 (q0), R1.1
unnamed: DRAM_CTRL1.42 (q1), R2.1
unnamed: DRAM_CTRL1.41 (q2), R3.1
unnamed: DRAM_CTRL1.40 (q3), R4.1
unnamed: DRAM_CTRL1.39 (q4), R5.1
unnamed: DRAM_CTRL1.37 (q5), R6.1
unnamed: DRAM_CTRL1.35 (q6), R7.1
unnamed: DRAM_CTRL1.34 (q7), R8.1
unnamed: DRAM_CTRL1.33 (q8), R9.1
unnamed: DRAM_CTRL1.32 (~cas), R10.1
unnamed: DRAM_CTRL1.28 (~ras0), R11.1
unnamed: DRAM_CTRL1.29 (~ras1), R12.1
unnamed: DRAM_CTRL1.30 (~ras2), R13.1
unnamed: DRAM_CTRL1.31 (~ras3), R14.1
unnamed: DRAM_CTRL1.45 (~win), R16.2
unnamed: DRI1.1 (OE), DRI2.1 (OE), U19.11
unnamed: DRO1.11 (Cp), DRO2.11 (Cp), U19.3
unnamed: INV1.10, U19.2
unnamed: INV1.13, U9.6
unnamed: R23.1, RB0.1 (G1), RB0.19 (G2), RB1.1 (G1), RB1.19 (G2), RB2.1 (G1), RB2.19 (G2), RB3.1 (G1), RB3.19 (G2), RB4.1 (G1), RB4.19 (G2), RB5.1 (G1), RB5.19 (G2), RB6.1 (G1), RB6.19 (G2), RB7.1 (G1), RB7.19 (G2)
unnamed: C42.1, RefCp1.5 (CV)
unnamed: R27.1, R28.2, RefCp1.7 (DIS)
unnamed: C16.1, R28.1, RefCp1.2 (TR), RefCp1.6 (THR)
unnamed: U3.3 (C), U5.13 (Q)
unnamed: U3.10 (~S), U9.3
unnamed: C43.2, U5.14 (Cext)
unnamed: C43.1, R31.1, U5.15 (RCext)
unnamed: R32.2, U5.10 (B), U5.11 (Clr)
unnamed: C47.2, U5.6 (Cext)
unnamed: C47.1, R33.2, U5.7 (RCext)
unnamed: U9.4, U9.11, U22.3 (C), U22.10 (~S)
unnamed: U20.5, U22.6 (~Q)
unnamed: U9.5, U22.9 (Q)
unnamed: INV1.4, prio0.12 (D1)
unnamed: INV1.6, prio0.13 (D2)
unnamed: INV1.8, prio0.2 (D3)
VCC: BB0.20 (VCC), BB1.20 (VCC), BB2.20 (VCC), BB3.20 (VCC), BB4.20 (VCC), BB5.20 (VCC), BB6.20 (VCC), BB7.20 (VCC), C0.1, C1.1, C2.1, C3.1, C4.1, C5.1, C6.1, C7.1, C8.1, C9.1, C10.1, C11.1, C12.1, C13.1, C14.1, C15.1, C17.1, C18.1, C19.1, C20.1, C21.1, C22.1, C23.1, C24.1, C25.1, C26.1, C27.1, C28.1, C29.1, C30.1, C31.1, C32.1, C33.1, C34.1, C35.1, C36.1, C37.1, C38.1, C39.1, C40.1, C41.1, C44.1, C45.1, C46.1, C49.1, C50.1, C51.1, C52.1, C53.1, C54.1, C55.1, C56.1, C57.1, C58.2, C59.2, C60.2, C61.2, C62.2, C63.2, C64.2, C65.2, C66.2, C67.2, C68.2, C69.2, C70.2, C71.2, C72.2, C73.2, C74.2, C75.2, C76.1, C77.1, C78.1, C79.1, C80.1, C81.1, C82.1, C83.1, C84.1, C85.2, C86.1, C87.2, C88.1, Cp1.1, Cp2.1, Cp3.1, Cp4.1, Cp5.1, Cp6.1, Cp7.1, Cp8.1, DR0.10 (vcc), DR1.10 (vcc), DR2.10 (vcc), DR3.10 (vcc), DR4.10 (vcc), DR5.10 (vcc), DR6.10 (vcc), DR7.10 (vcc), DR8.10 (vcc), DR9.10 (vcc), DR10.10 (vcc), DR11.10 (vcc), DR12.10 (vcc), DR13.10 (vcc), DR14.10 (vcc), DR15.10 (vcc), DRAM1.AA2, DRAM1.BA2, DRAM1.CA2, DRAM1.DA2, DRAM1.V1 (VCC), DRAM1.V2 (VCC), DRAM1.V3 (VCC), DRAM1.V4 (VCC), DRAM1.V5 (VCC), DRAM1.V6 (VCC), DRAM1.V7 (VCC), DRAM1.V8 (VCC), DRAM1.V10, DRAM1.V11, DRAM1.V12, DRAM1.V13, DRAM1.V14, DRAM1.V15, DRAM1.V16, DRAM1.V17, DRAM1.V18, DRAM1.V19, DRAM1.V20, DRAM1.V21, DRAM1.V22, DRAM1.V23, DRAM1.V24, DRAM_CTRL1.36 (vcc), DRI1.20 (VCC), DRI2.20 (VCC), DRO1.20 (VCC), DRO2.20 (VCC), DramSM1.20 (VCC), INV1.14 (VCC), R15.1, R16.1, R27.2, R29.1, R30.1, R31.2, R32.1, R33.1, R35.2, R36.1, RB0.20 (VCC), RB1.20 (VCC), RB2.20 (VCC), RB3.20 (VCC), RB4.20 (VCC), RB5.20 (VCC), RB6.20 (VCC), RB7.20 (VCC), RN1.1 (common), RN2.1 (common), RN3.1 (common), RamClk1.14 (Vcc), RamClk2.8 (Vcc), RefCp1.4 (R), RefCp1.8 (VCC), U2.16 (VCC), U3.14 (VCC), U4.20 (VCC), U5.16 (VCC), U6.20 (VCC), U9.14 (VCC), U19.14 (VCC), U20.14 (VCC), U22.14 (VCC), prio0.14 (vcc)

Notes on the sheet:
Alternative 0805-size SMD decoupling caps
Alternative oscillator
New design RAM board. Replaces M64R, M64L, M128R & M128L boards in original Lilith. As in the old design : -- write access is 16bit wide @ 1M words -- read access is either 64bit wide @ 256K words (IFU,DSP) -- or 16 bit wide @ 1M words
ca 64 KHz

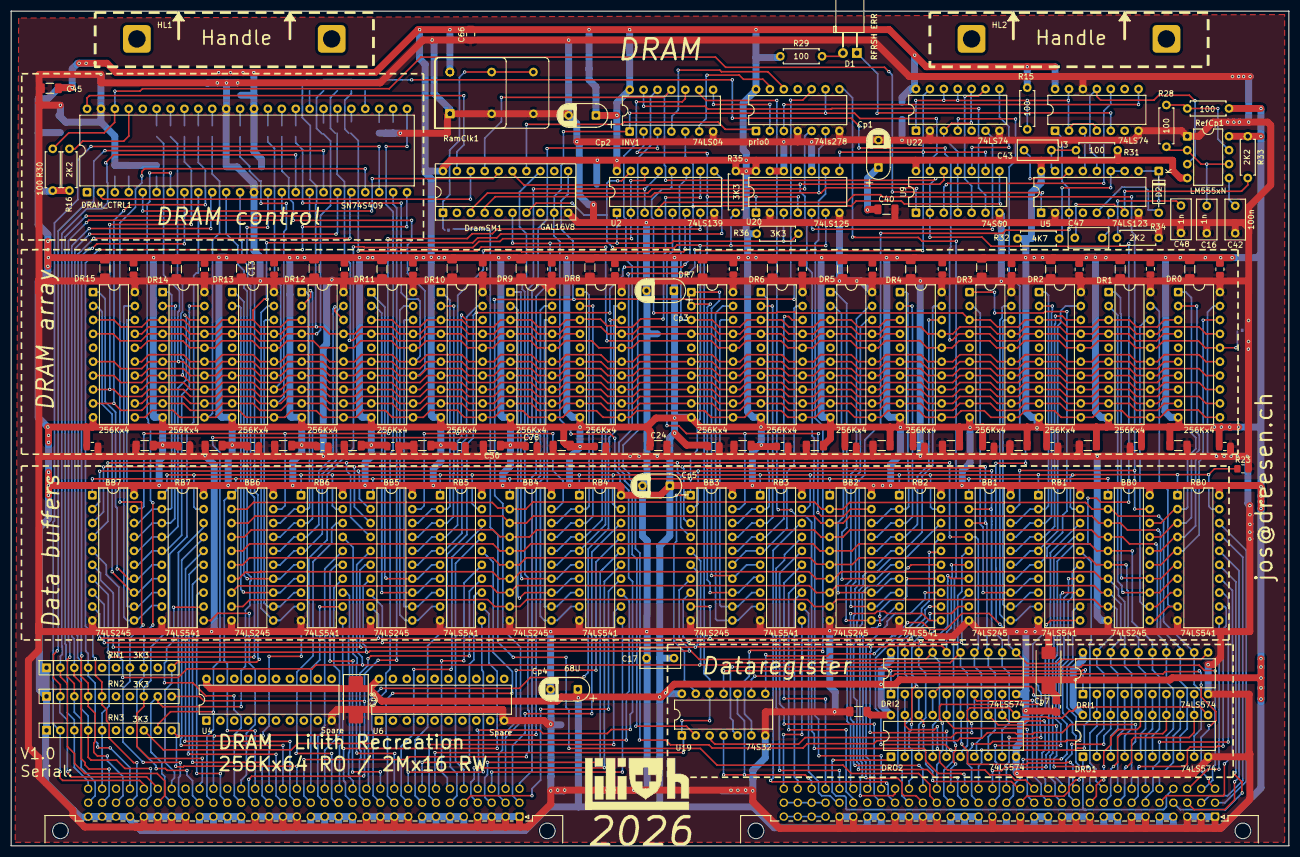
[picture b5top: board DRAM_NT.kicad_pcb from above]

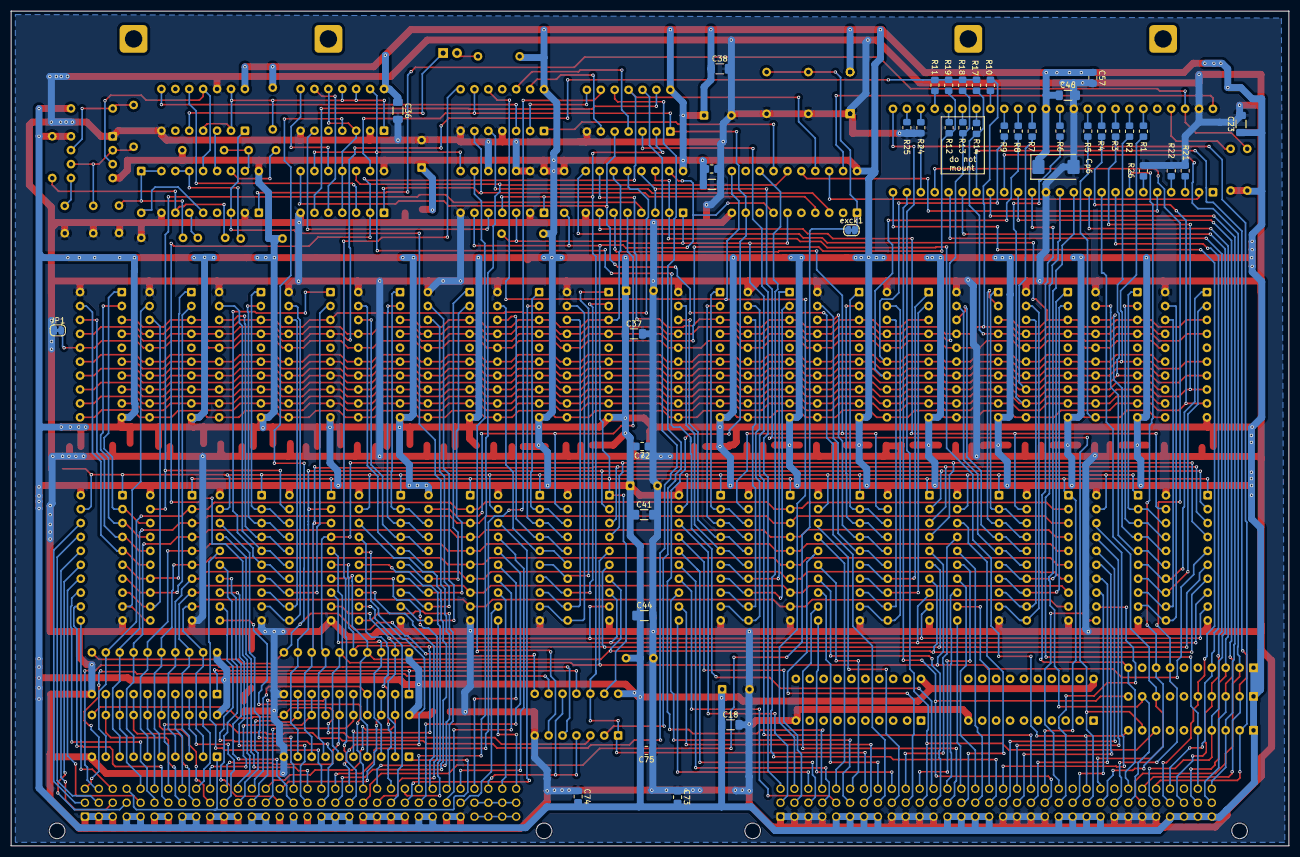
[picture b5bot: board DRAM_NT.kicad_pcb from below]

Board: 2 copper layers, 233.3 x 152.4 mm, 194 parts (40 on the bottom side), 286 nets.
